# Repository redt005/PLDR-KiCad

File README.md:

# PLDR-KiCad
---
## NUCLEO64-G474RE - No Connection Pins:

PB8-BOOT0 - Boot Select + GPIO:
Using PB8 as PWM output from TIM8 -> NC for no IO on PB8-BOOT0

PA13 and PA14 - Serial Wire Debug:
Used by ST-LINK for SWD + flashing user code through USB -> NC so no IO towards SWD functions outside of USB

PA15 - Shared pin with PC0/PA15:
PC0/PA15 uses PC0 for TIM1 PWM output -> NC for no IO from PA15

PC14, PC15, PF0, and PF1 - Low/High Speed Clock Input/Output:
Used by Nucleo board circuit to route onboard crystal signals -> NC to prevent IO to and from the crystals to the rest of the board

NRST - Internal Reset:
Will program resets within code and default faults -> NC to prevent signals from accidentaly reseting MCU

PC4, PC4/PA2, and PC5/PA3 - Shared with PA2 and PA3:
Communication of PA2/PA3 is done through VCOM port and the pins themselves but PC4/PC5 do overlap them -> NC PC4/PC5 for no IO from those pins and let the LPUART pins do their own thing

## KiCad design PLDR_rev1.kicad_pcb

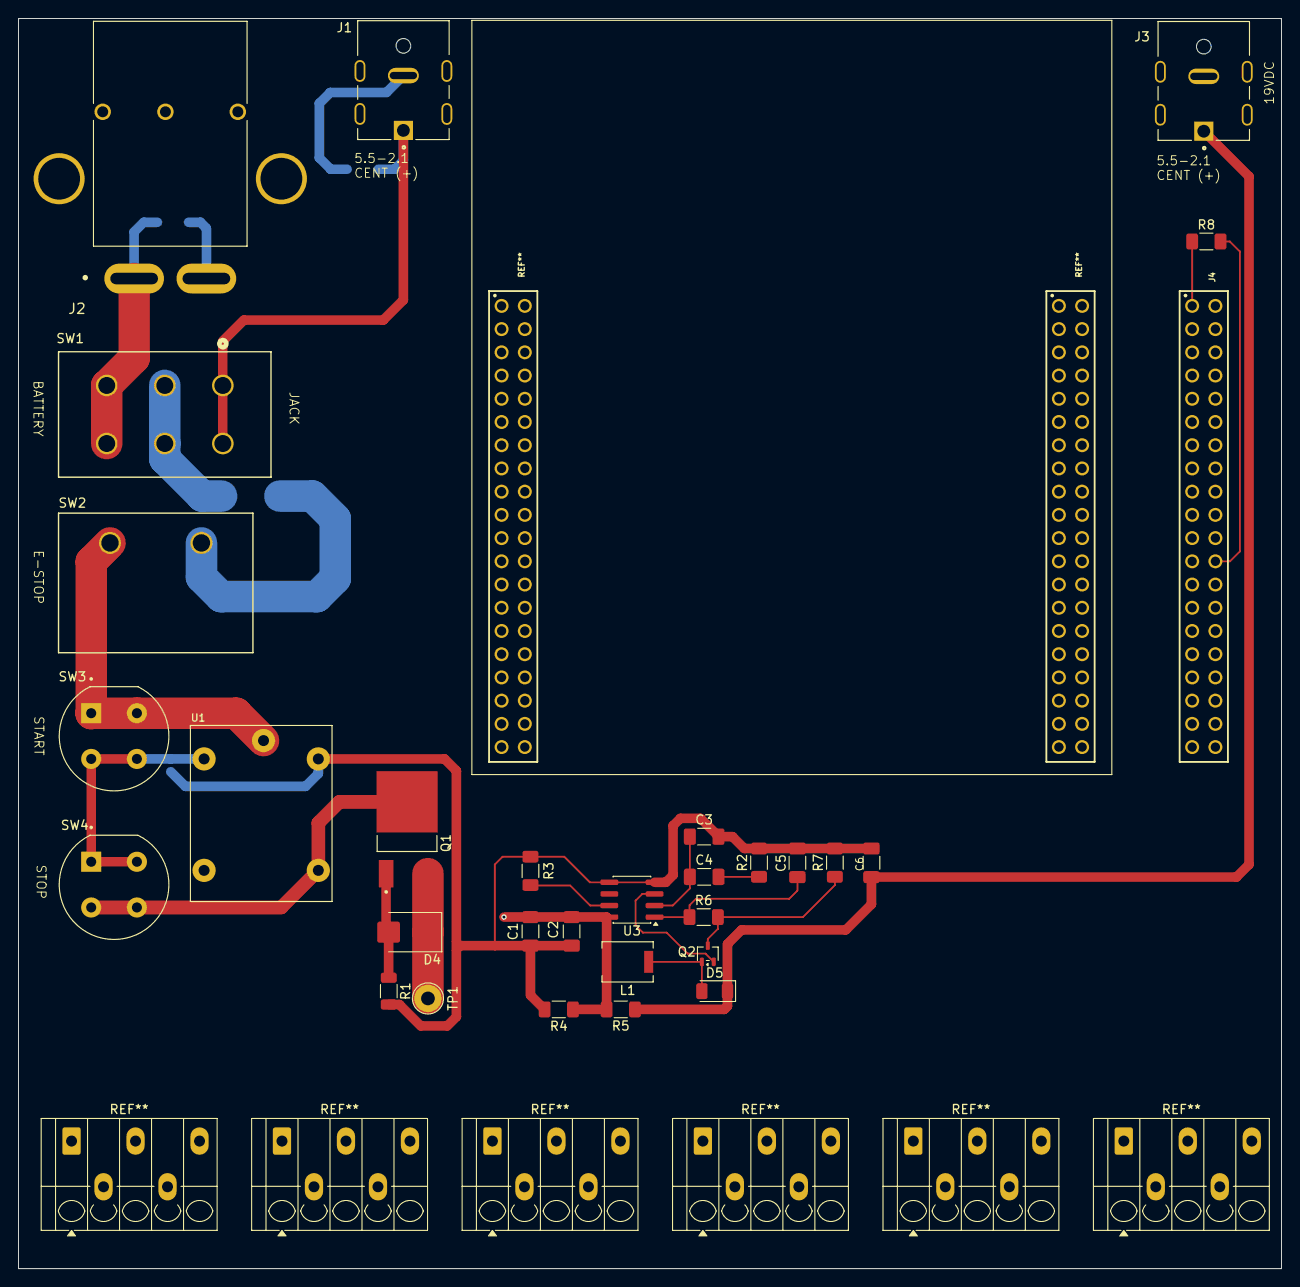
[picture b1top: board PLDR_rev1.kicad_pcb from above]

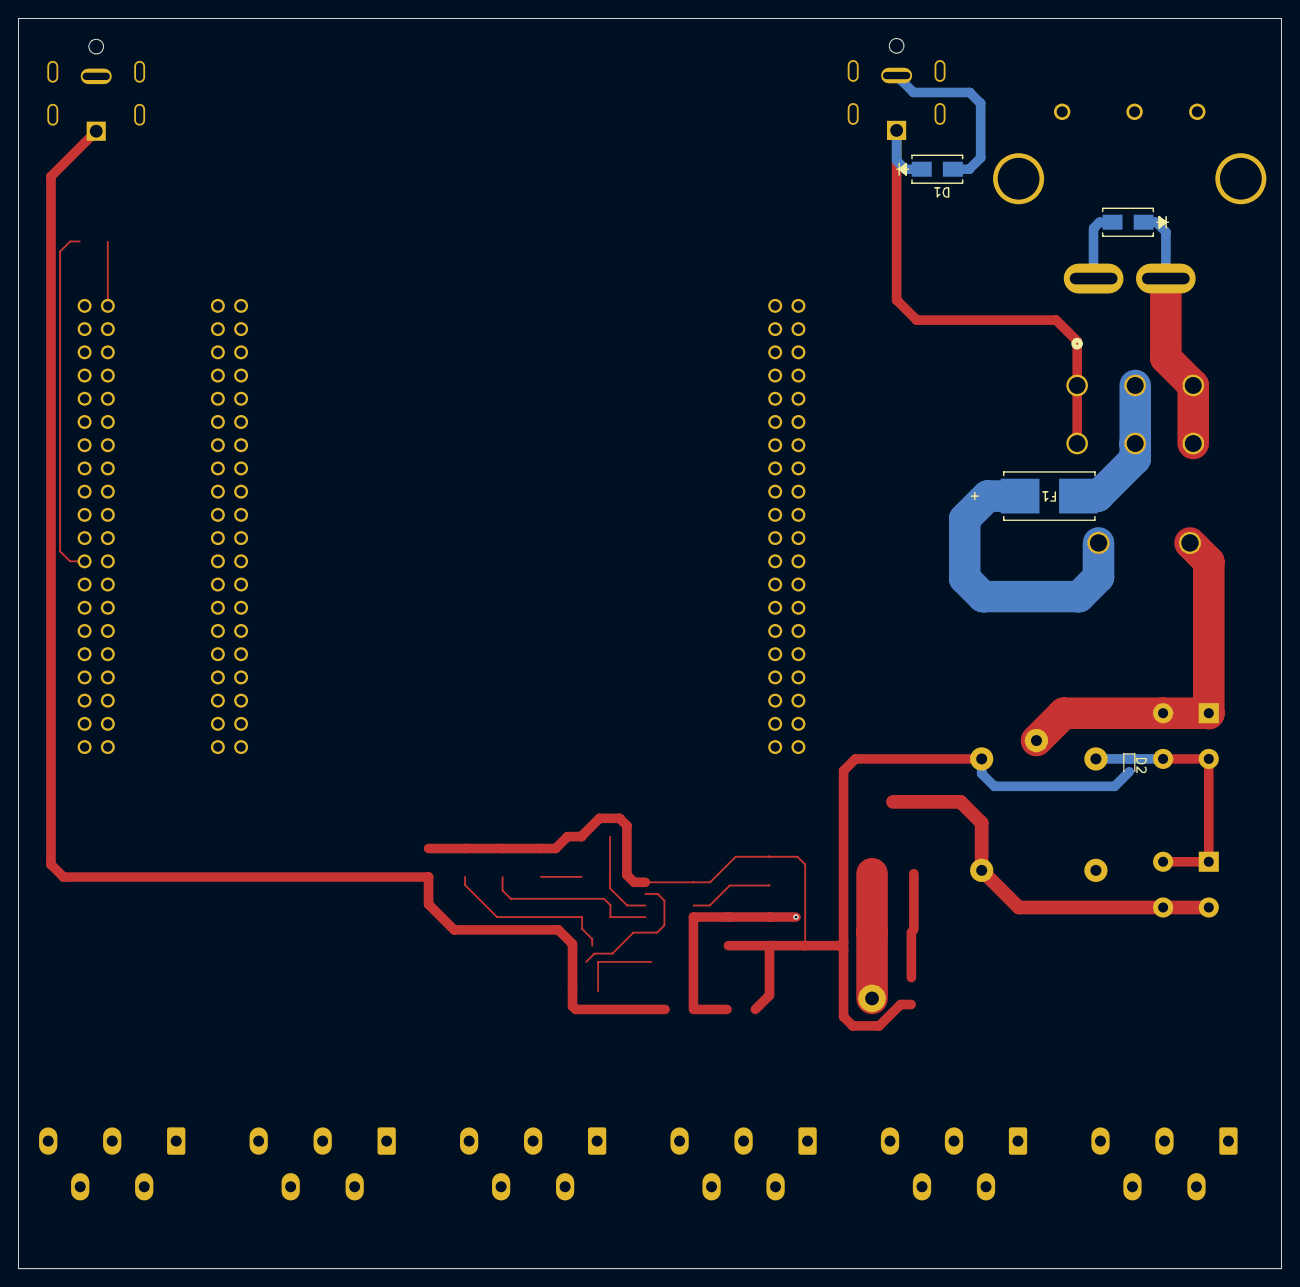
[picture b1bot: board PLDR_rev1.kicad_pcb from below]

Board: 4 copper layers, 138.1 x 136.7 mm, 34 parts (4 on the bottom side), 21 nets.

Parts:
C1: 220uF; C_1206_3216Metric_Pad1.33x1.80mm_HandSolder
C2: 100nF; C_1206_3216Metric_Pad1.33x1.80mm_HandSolder
C3: 2.2nF; C_1206_3216Metric_Pad1.33x1.80mm_HandSolder
C4: 39nF; C_1206_3216Metric_Pad1.33x1.80mm_HandSolder
C5: 10pF; C_1206_3216Metric_Pad1.33x1.80mm_HandSolder
C6: 82uF; C_1206_3216Metric_Pad1.33x1.80mm_HandSolder
D1, D3: SMAJ13A; SMASeries_LTF
D2: 1N914WT; D_SOD-523
D4: SMBJ5349B-TP; D_SMB
D5: D_Schottky; D_1206_3216Metric
F1: Fuse 10A; 0154Series_LTF
J1: JACK-C-PC-10A-RA_R_; GLOBTECK_JACK-C-PC-10A-RA_R_
J2: ASMPR45-1X2-RK; APP_ASMPR45-1X2-RK
J3: Screw_Terminal_01x02; GLOBTECK_JACK-C-PC-10A-RA_R_
J4: Conn_02x20_Odd_Even_MountingPin; 61304021821
L1: 4.7uH; L_Neosid_Ms42
Q1: NDT456P; DIO_FERD20H100SB-TR
Q2: Q_NMOS; SOT-323_SC-70
R1: 100k; R_1206_3216Metric
R2: 2.37k; R_1206_3216Metric_Pad1.30x1.75mm_HandSolder
R3: 26.7k; R_1206_3216Metric_Pad1.30x1.75mm_HandSolder
R4: 976; R_1206_3216Metric_Pad1.30x1.75mm_HandSolder
R5: 14.7k; R_1206_3216Metric_Pad1.30x1.75mm_HandSolder
R6: 100; R_1206_3216Metric_Pad1.30x1.75mm_HandSolder
R7: 6m; R_1206_3216Metric_Pad1.30x1.75mm_HandSolder
R8: 1k; R_1206_3216Metric_Pad1.30x1.75mm_HandSolder
SW1: S602031MS02Q; S602031MS02Q_CNK
SW2: E-Stop; SW_A8L-11_OMR
SW3: Start; SW_D6R90_F2_LFS
SW4: Stop; SW_D6R90_F2_LFS
TP1: Unregulated 12V Test Point; TestPoint_Loop_D2.54mm_Drill1.5mm_Beaded
U1: AZ943-1CH-12DE
U3: LM3478MA; SOIC-8_3.9x4.9mm_P1.27mm

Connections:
+3V3: J4.1, R8.1
+5V: J4.2, J4.4
+12V: C1.1, C2.1, D4.1 (K), L1.1, Q1.3 (S), R4.1, R5.1, TP1.1 (1_1), U3.8 (V_{IN})
/Jetson Header/SPI2_NSS: J4.24, R8.2
GND: C1.2, C2.2, C3.2, C5.2, C6.2, D1.2, D2.2 (A), D3.2, J1.2, J2.2, J3.2, J4.6, J4.9, J4.14, J4.20, J4.25, J4.30, R1.2, R2.2, R3.2, R4.2, R7.2, U1.P2 (2), U3.4 (AGND), U3.5 (PGND)
unnamed: C4.2, R2.1
unnamed: D1.1, J1.1, SW1.1, SW1.4
unnamed: D2.1 (K), SW3.2, SW4.1 (A), U1.P5 (5)
unnamed: D3.1, J2.1, SW1.3, SW1.6
unnamed: D4.2 (A), Q1.1 (G), R1.1
unnamed: D5.2 (A), L1.2, Q2.1 (D)
unnamed: C6.1, D5.1 (K), J3.1, R5.2
unnamed: F1.2, SW1.2, SW1.5
unnamed: Q1.2 (D), SW4.2 (B), U1.P3 (3)
unnamed: Q2.2 (G), U3.3 (FB)
unnamed: Q2.3 (S), R6.2, R7.1
unnamed: F1.1, SW2.1 (A)
unnamed: SW2.2 (B), SW3.1, U1.P9 (1)
unnamed: C3.1, C4.1, U3.2 (COMP)
unnamed: R3.1, U3.7 (FA/SD)
unnamed: C5.1, R6.1, U3.1 (I_{SEN})

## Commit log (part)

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2026-06-14 - Changed conceptual overview diagram. - Added project part libraries -JACK-C-PC-10A-RA(R) -S602031MS02Q -ASMPR45-1X2-RK -ALQ3F12 - Added LM3478_Boost schematic - Added power selector switch to Batte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
